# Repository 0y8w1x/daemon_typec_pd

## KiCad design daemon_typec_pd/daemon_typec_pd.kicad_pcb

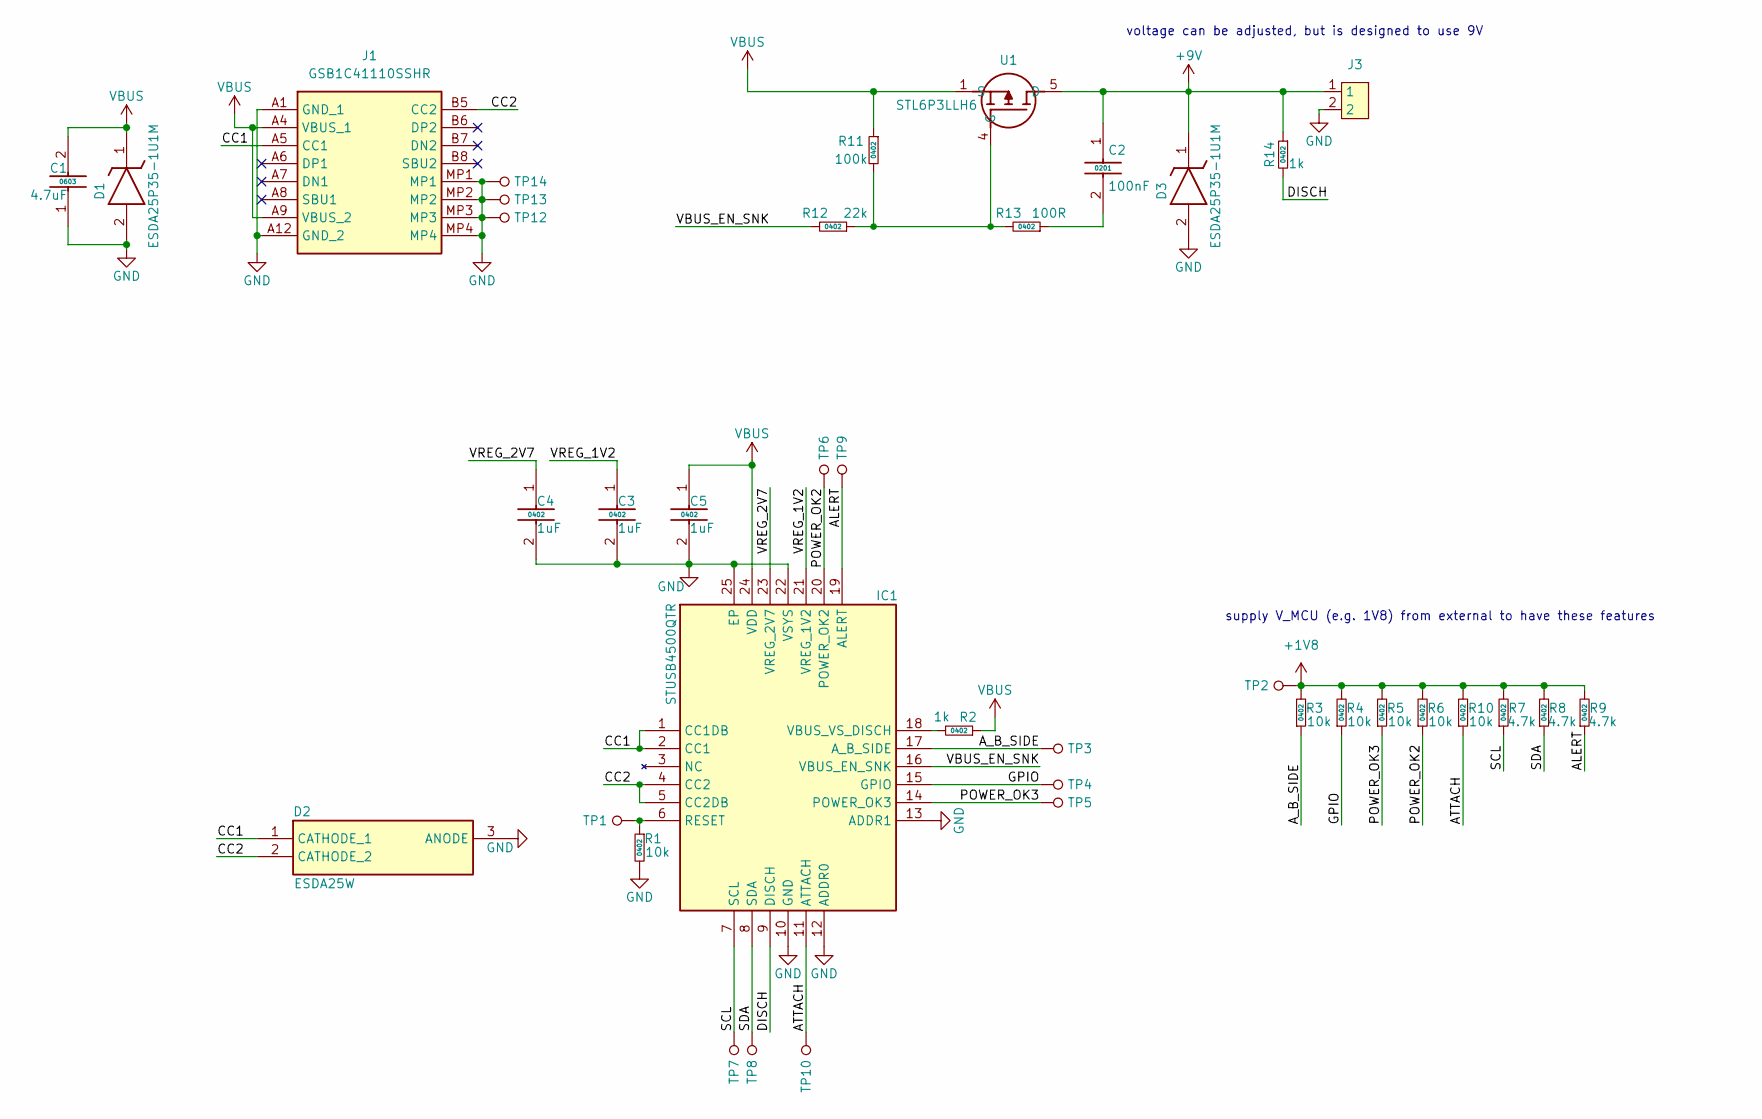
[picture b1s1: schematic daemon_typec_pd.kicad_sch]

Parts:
C1: 4.7uF; CAPC1608X90N; Manufacturer_Part_Number GRM188Z71C475KE21D; Mouser Part Number 81-GRM188Z71C475KE1D
C2: 100nF; CAPC0603X33N; Manufacturer_Part_Number GRM033R61E104KE14J; Mouser Part Number 81-GRM033R61E104KE4J
C3, C4, C5: 1uF; CAPC1005X55N; Manufacturer_Part_Number GRM155C71C105KE11J; Mouser Part Number 81-GRM155C71C105KE11
D1, D3: ESDA25P35-1U1M; ESDA25P351U1M; Manufacturer_Part_Number ESDA25P35-1U1M; Mouser Part Number 511-ESDA25P35-1U1M
D2: ESDA25W; SOT65P210X110-3N; Manufacturer_Part_Number ESDA25W; Mouser Part Number 511-ESDA25W
IC1: STUSB4500QTR; QFN50P400X400X100-25N-D; Manufacturer_Part_Number STUSB4500QTR; Mouser Part Number 511-STUSB4500QTR
J1: GSB1C41110SSHR; Manufacturer_Part_Number GSB1C41110SSHR
J3: pin_header_male_2pin
R1, R3, R4, R5, R6, R10: 10k; 0402_res
R2, R14: 1k; 0402_res
R7, R8, R9: 4.7k; 0402_res
R11: 100k; 0402_res
R12: 22k; 0402_res
R13: 100R; 0402_res
TP1, TP2, TP3, TP4, TP5, TP6, TP7, TP8, TP9, TP10, TP12, TP13, TP14: tp_1mm
U1: STL6P3LLH6

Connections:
+1V8: R3.2, R4.2, R5.2, R6.2, R7.2, R8.2, R9.2, R10.2, TP2.1
+9V: C2.1, D3.1 (K), J3.1, R14.1, U1.5 (D)
/ALERT: IC1.19 (ALERT), R9.1, TP9.1
/ATTACH: IC1.11 (ATTACH), R10.1, TP10.1
/A_B_SIDE: IC1.17 (A_B_SIDE), R3.1, TP3.1
/CC1: D2.1 (CATHODE_1), IC1.1 (CC1DB), IC1.2 (CC1), J1.A5 (CC1)
/CC2: D2.2 (CATHODE_2), IC1.4 (CC2), IC1.5 (CC2DB), J1.B5 (CC2)
/DISCH: IC1.9 (DISCH), R14.2
/GPIO: IC1.15 (GPIO), R4.1, TP4.1
/POWER_OK2: IC1.20 (POWER_OK2), R6.1, TP6.1
/POWER_OK3: IC1.14 (POWER_OK3), R5.1, TP5.1
/SCL: IC1.7 (SCL), R7.1, TP7.1
/SDA: IC1.8 (SDA), R8.1, TP8.1
/VBUS_EN_SNK: IC1.16 (VBUS_EN_SNK), R12.2
/VREG_1V2: C3.1, IC1.21 (VREG_1V2)
/VREG_2V7: C4.1, IC1.23 (VREG_2V7)
GND: C1.1, C3.2, C4.2, C5.2, D1.2 (A), D2.3 (ANODE), D3.2 (A), IC1.10 (GND), IC1.12 (ADDR0), IC1.13 (ADDR1), IC1.22 (VSYS), IC1.25 (EP), J1.A1 (GND_1), J1.A12 (GND_2), J1.MP1, J1.MP2, J1.MP3, J1.MP4, J3.2, R1.2, TP12.1, TP13.1, TP14.1
unnamed: C2.2, R13.1
unnamed: IC1.6 (RESET), R1.1, TP1.1
unnamed: IC1.18 (VBUS_VS_DISCH), R2.2
unnamed: R11.2, R12.1, R13.2, U1.4 (G)
VBUS: C1.2, C5.1, D1.1 (K), IC1.24 (VDD), J1.A4 (VBUS_1), J1.A9 (VBUS_2), R2.1, R11.1, U1.1 (S), U1.2 (S), U1.3 (S)

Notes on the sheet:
supply V_MCU (e.g. 1V8) from external to have these features
voltage can be adjusted, but is designed to use 9V

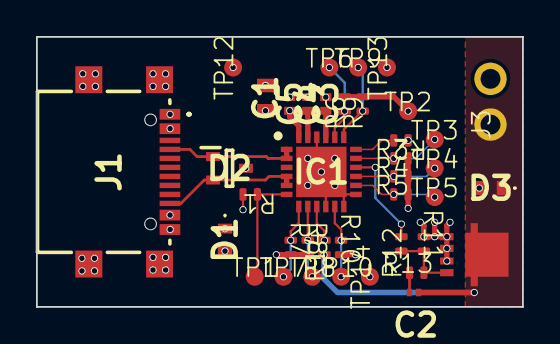
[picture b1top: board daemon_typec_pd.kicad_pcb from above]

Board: 4 copper layers, 27.0 x 15.0 mm, 39 parts (0 on the bottom side), 22 nets.

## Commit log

2024-05-02 init
2024-07-27 changed files
